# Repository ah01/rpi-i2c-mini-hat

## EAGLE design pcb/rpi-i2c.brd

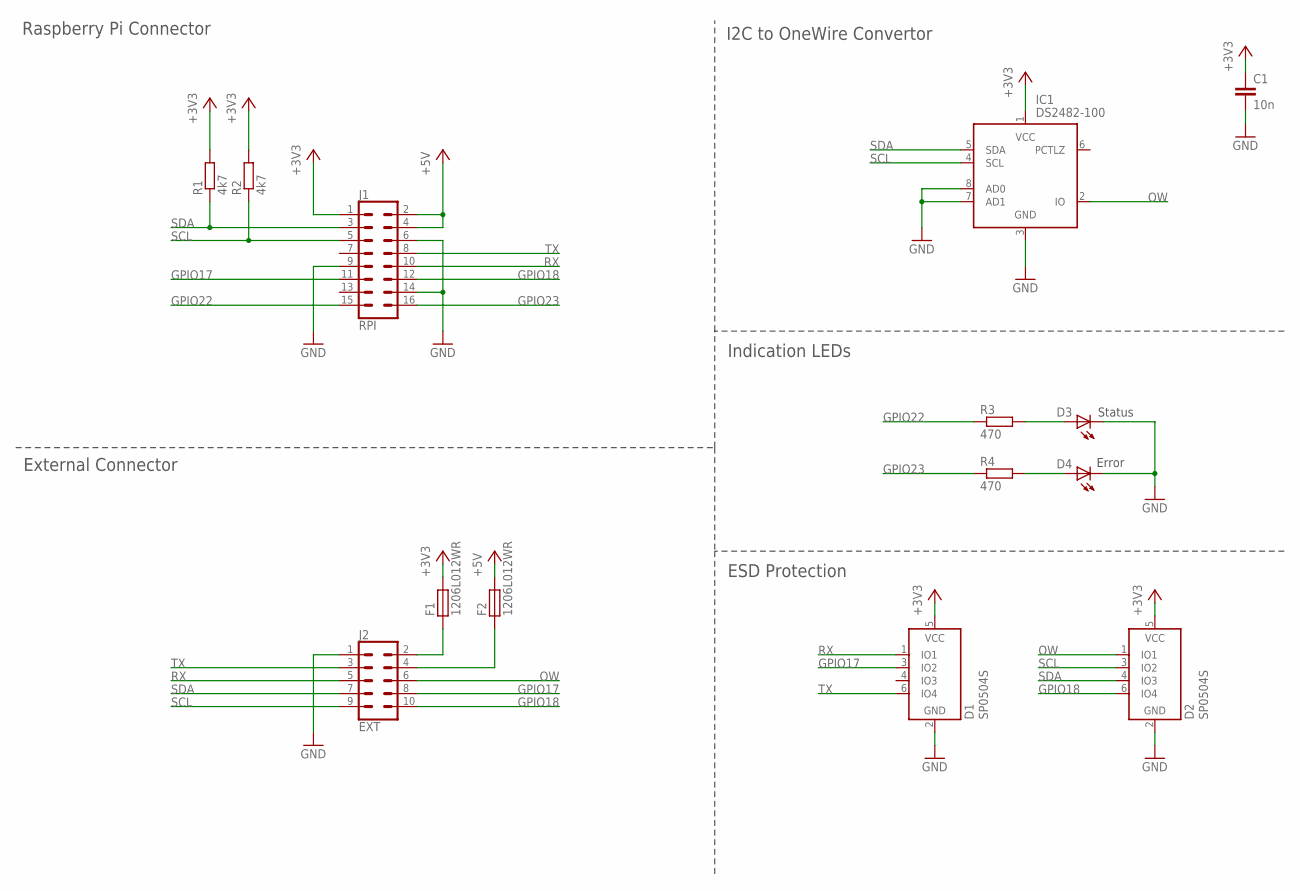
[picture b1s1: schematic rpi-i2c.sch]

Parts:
C1: 10n; C0805
D1, D2: SP0504S; SOT23-6
D3, D4: LEDCHIPLED_0805; CHIPLED_0805
F1, F2: 1206L012WR; C1206K
IC1: DS2482-100; SO08
J1: RPI; 2X8-INVERSE
J2: EXT; 30310-5002HB
R1, R2: 4k7; R0603
R3, R4: 470; R0603

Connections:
3V3F: F1.1, J2.2
5V0F: F2.1, J2.4
+3V3: C1.1, D1.5 (VCC), D2.5 (VCC), F1.2, IC1.1 (VCC), J1.1, R1.2, R2.2
+5V: F2.2, J1.2, J1.4
GND: C1.2, D1.2 (GND), D2.2 (GND), D3.C, D4.C, IC1.3 (GND), IC1.7 (AD1), IC1.8 (AD0), J1.6, J1.9, J1.14, J2.1
GPIO17: D1.3 (IO2), J1.11, J2.8
GPIO18: D2.6 (IO4), J1.12, J2.10
GPIO22: J1.15, R3.2
GPIO23: J1.16, R4.2
unnamed: D3.A, R3.1
unnamed: D4.A, R4.1
OW: D2.1 (IO1), IC1.2 (IO), J2.6
RX: D1.1 (IO1), J1.10, J2.5
SCL: D2.3 (IO2), IC1.4 (SCL), J1.5, J2.9, R2.1
SDA: D2.4 (IO3), IC1.5 (SDA), J1.3, J2.7, R1.1
TX: D1.6 (IO4), J1.8, J2.3

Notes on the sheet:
Raspberry Pi Connector
External Connector
I2C to OneWire Convertor
Indication LEDs
ESD Protection
Status
Error

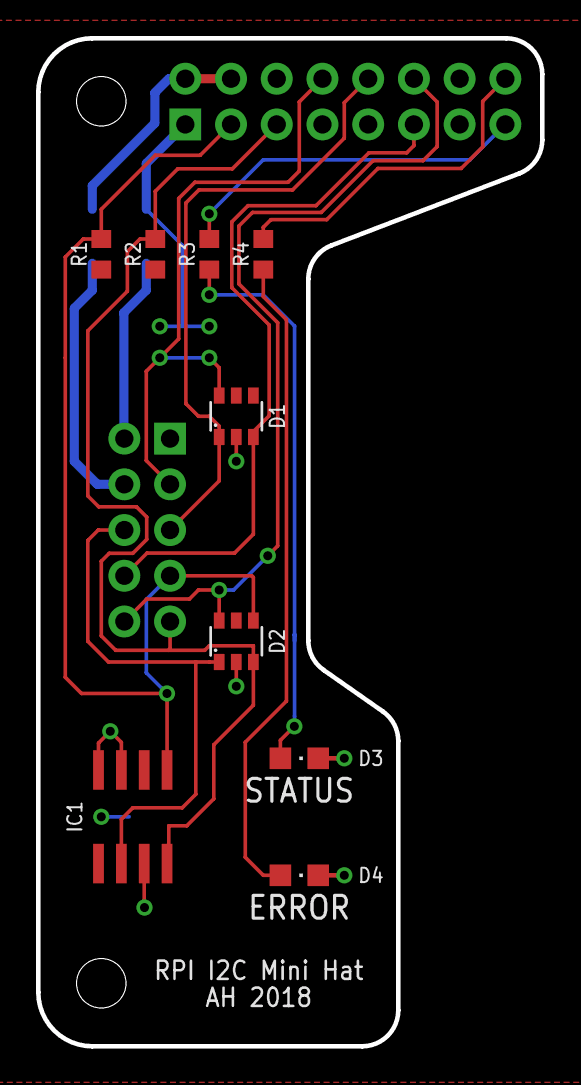
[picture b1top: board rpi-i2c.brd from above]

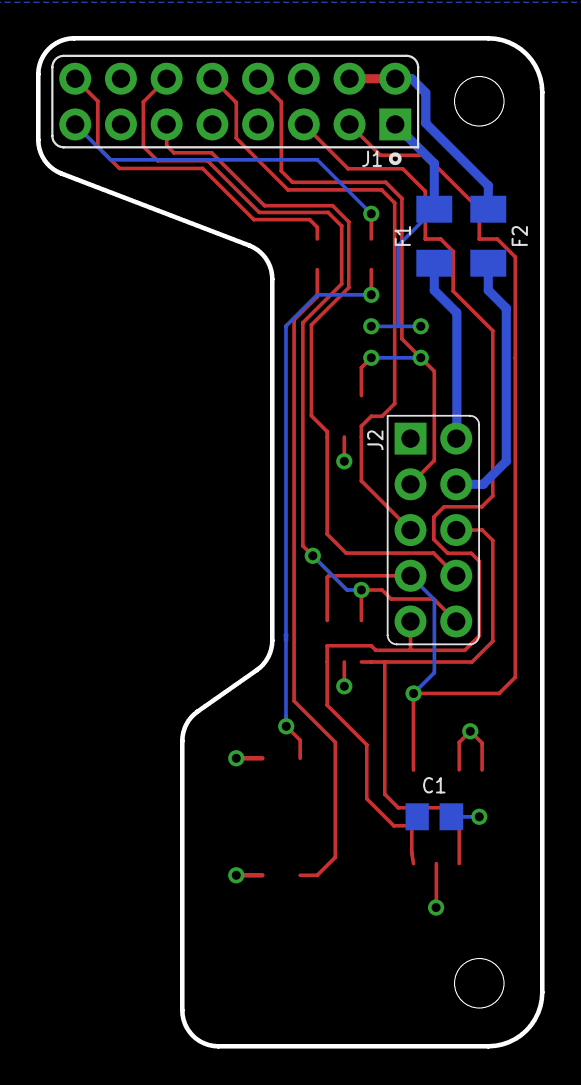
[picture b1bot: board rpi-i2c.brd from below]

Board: 2 copper layers, 28.0 x 56.0 mm, 14 parts (5 on the bottom side), 16 nets.

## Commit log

2019-01-12 Add original PCB (version used for order PCB)
2019-01-12 Clean up schematics and save PCB image.
2019-01-12 Add BOM
2019-02-13 Add photos of physical hat
2019-02-13 RPI photo
2019-02-13 Panel STL file
2019-02-13 3d object images
2019-02-13 Screen shots
2019-02-14 Add log
2019-02-14 Add link to raw image
2019-02-14 Add images
2019-02-14 Add photos to log
